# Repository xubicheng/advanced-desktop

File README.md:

# AD — 鼠标形态的无屏微型计算机

**一句话：把一台计算机做进鼠标里。没有屏幕，用语音进出，屏幕是可选外设。**

> 现状：**设计方案阶段（v4），未采购、未下单，没有可运行的样机。**
> 这不是成品仓库，是一份把「能不能做、要妥协什么」算清楚的工程档案。

---

## 这是什么

AD = Advanced Desktop，一个 DIY 研究项目：

- **硬件**：BeagleBone Black（L1 板级开源）塞进 132×76×40mm 的真鼠标外壳，重 250–300g；
- **交互**：按住说话 → 云端 STT → LLM → 云端 TTS → 喇叭播报；自身位移驱动光标；
- **屏幕**：**可选**。要么 BBB 用 micro-HDMI 直出 720p，要么由 Android 手机把 AD 自己的画面投到你的 PC 显示器上；
- **软件**：一份 Rust 核心 + 两个渲染器（Android Canvas / BBB egui）+ 一个 PC 端 Receiver（只显示帧、只注入鼠标）。

**Windows / Linux 上跑的不是「AD 的另一个版本」，只是「一台显示器 + 一只被遥控的鼠标」。**

---

## 当前阶段

| 项 | 状态 |
|---|---|
| 硬件方案 | ✅ 定稿（v3）：BBB + 720p + 成品 USB 鼠标模块 + DC 5V/4A |
| 投屏方案 | ✅ 定稿（v4）：自渲染 + 自有 Receiver（MJPEG over TCP），scrcpy 兜底 |
| Android 最小链路 | ⬜ 未开始（计划 2 周） |
| 投屏 + 反向指针 | ⬜ 未开始（计划 W3–W4） |
| BBB 硬件端 | ⬜ 未开始（等板） |
| 采购 | ⬜ **未下单**（清单已出） |

## 下一步

1. 询价 BeagleBone Black（买不到就走 BBB Wireless）；
2. 按 [Android 先行周计划](docs/v3/Android-先行-周计划.md) 跑 W1–W2 语音链路；
3. W3 投屏、W4 反向指针；
4. 硬件端最后接。

---

## 文档索引

| 文档 | 看什么 |
|---|---|
| [**v4 方案（当前）**](docs/v4/AD-鼠标形无屏微型计算机-设计方案-v4.md) | 概念模型、投屏三方案取舍、数据流图、反向输入、息屏实测 |
| [v3 方案（硬件基线）](docs/v3/AD-鼠标形无屏微型计算机-设计方案-v3.md) | 六项连带代价、720p、USB Hub、供电、散热重算、验收表 |
| [Android 先行周计划](docs/v3/Android-先行-周计划.md) | 2 周排期 + 15 条验收线 |
| [许可清单](docs/v3/许可清单.md) | 组件许可、GPL 隔离、模型权重核实状态 |
| [采购清单（淘宝优先）](docs/v3/采购清单-淘宝优先.md) | 表 A 淘宝 / 表 B 线下 / 总预算 |
| [MVP 手工样品清单](docs/MVP-checklist/MVP-手工样品实施清单.md) | 买料 → 焊 → 装 → 测，每步通过标准 |
| [**决策记录 DECISIONS**](docs/DECISIONS.md) | D1–D5 为什么这么定，以及没关闭的问题 |
| [变更记录 CHANGELOG](docs/CHANGELOG.md) | v1→v4 每次改了什么、为什么、推翻了什么 |
| [文档总索引](docs/README.md) | 全部文档的导航 |

---

## 三个必须先知道的硬事实

1. **单核 1GHz + 512MB 跑不动本地语音。** 3 秒音频在 BBB 上要 9–15 秒才出结果。所以语音默认走云端，本地只留 6–10 条预录提示音。这不是偷懒，是算力事实。
2. **720p 是上限。** TDA19988 与单核显示子系统撑不住 1080p 的日常使用，UI 按 1280×720 设计（正文 ≥24px、按钮 ≥64px、禁双栏）。
3. **鼠标会很重（250–300g）。** 常规重鼠约 120–140g。这是「L1 开源板 + 真鼠标形态」的必然代价，缓解手段是重心压在掌心，不是减重。

---

## 在手机上看进度

**客户端的账号同步不是本仓库能控制的**——你在 A 电脑上的对话不会自动出现在 B 电脑或手机上。

本项目的跨设备查看机制是：**GitHub 公开仓库 + 每次更新即提交。**

手机上：

1. 用手机浏览器打开 <https://github.com/xubicheng/advanced-desktop>；
2. 点 **Commits** 看最近改了什么（每条提交信息都写清改了什么）；
3. 看根目录 **README** 的「当前阶段」表格 —— 这张表每次更新都会改；
4. 想看细节就点 `docs/` 下的 Markdown，GitHub 手机版能直接渲染。

不需要装 App，不需要登录。

---

## 目录结构

```
advanced-desktop/
├─ docs/        v1 / v2 / v3 / v4 版本化方案 + CHANGELOG + DECISIONS + README 索引
├─ software/    核心（Rust）/ Android 壳 / BBB 壳 / PC Receiver
├─ hardware/    外壳（FreeCAD/OpenSCAD）、转接板（KiCad）、装配图
├─ bom/         采购清单 CSV（淘宝 / 线下）
└─ logs/        对话纪要（已脱敏）
```

---

## 许可

- 代码 **MIT**（[LICENSE-CODE](LICENSE-CODE)）
- 硬件设计 **CERN-OHL-S-2.0**（[LICENSE-HARDWARE](LICENSE-HARDWARE)）
- 文档 **CC-BY-4.0**（[LICENSE-DOCS](LICENSE-DOCS)）
- 说明与第三方组件：[LICENSE](LICENSE)、[THIRD-PARTY.md](THIRD-PARTY.md)

## 兼容基线

| 平台 | 支持 |
|---|---|
| Windows | 10 1809（17763）+、Windows 11 |
| Linux | glibc ≥ 2.28：Ubuntu 20.04/22.04/24.04、Rocky 8/9、Alma 8/9 |
| Linux（不支持） | **CentOS 7（glibc 2.17，已 EOL）**、CentOS 8（已 EOL） |
| Android | 8.0（API 26）+ |
| macOS / iOS | 不做 |

---

*这是一个仍在设计阶段的 DIY 项目。所有价格、供货、性能数字凡未实测的都已标注「需询价 / 需实测」。*

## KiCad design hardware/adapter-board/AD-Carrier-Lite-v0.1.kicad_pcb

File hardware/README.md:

# hardware/ — 外壳、转接板、装配图

```
hardware/
├─ enclosure/        外壳：FreeCAD 参数化模型 + OpenSCAD 备选 + 打印参数
├─ adapter-board/    载板/转接板：KiCad 工程（电源保护 + Hub 供电 + 排针 + 按键）
└─ assembly/         装配图、爆炸图、螺丝与走线表
```

## 状态

- `adapter-board/`：**Carrier-Lite v0.1 草案已出板**（60×45mm，2 层），含 Gerber、BOM、坐标、STEP、预览与制板说明，见 [FAB-NOTES.md](adapter-board/FAB-NOTES.md)。未出原理图，尺寸待实测。
- `enclosure/`、`assembly/`：**仍为空骨架。** 设计参数已定，图纸尚未出。

## 已定的关键参数（照此建模）

| 项 | 值 | 出处 |
|---|---|---|
| 外形 | **132 × 76 × 40 mm** | v3 §3.1 |
| 内部净高 | ≥ 24 mm（RJ45 13.5mm 为最高元件） | v3 §3.1 |
| 主板 | BeagleBone Black，86.36 × 53.34 × 1.6 mm | 官方 |
| 壁厚 | 2.4–3.0 mm | v3 §6.2 |
| 材质 | **ABS**（主体）+ **5052 铝 1.5mm**（底盖兼配重） | v3 §6.2 |
| 开孔率 | 总 3.3–3.6%（侧面进风 φ2×6×2，底部后段出风 φ2×12） | v3 §6.3 |
| 顶面 | **不开孔**（手感 / 进灰 / 烫手） | v3 §6.3 |
| 散热片 | 铝 20×20×8 + 导热垫 1.0mm ≥3W/mK | v3 §6.4 |
| 光学高度 | 按实测的鼠标模块定，配 0.5/1.0/1.5mm 三档垫片 | v3 §4.4 |

## 许可

**CERN-OHL-S-2.0**（强互惠）。改过的设计必须以同一许可公开。

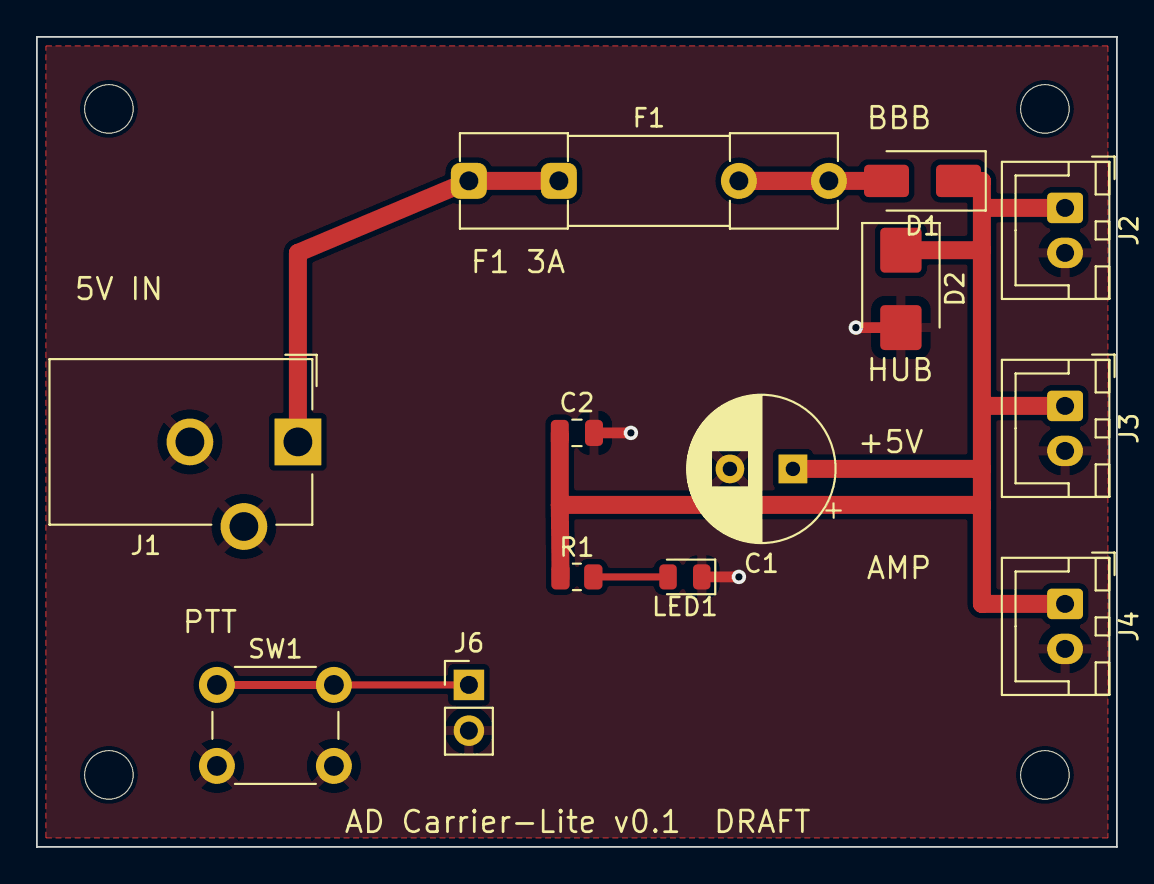
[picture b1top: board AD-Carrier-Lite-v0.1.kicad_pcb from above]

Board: 2 copper layers, 60.0 x 45.0 mm, 17 parts (0 on the bottom side), 6 nets.

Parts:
C1: 470uF 10V; CP_Radial_D8.0mm_P3.50mm
C2: 100nF 50V; C_0805_2012Metric
D1: SS54; D_SMA
D2: SMAJ5.0A; D_SMB
F1: 3A slow-blow; Fuseholder_Clip-5x20mm_Littelfuse_111_Inline_P20.00x5.00mm_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
H1, H2, H3, H4: MountingHole_2.7mm_M2.5
J1: DC 5.5x2.1; BarrelJack_CUI_PJ-102AH_Horizontal
J2: 5V OUT BBB; JST_XH_B2B-XH-A_1x02_P2.50mm_Vertical
J3: 5V OUT HUB; JST_XH_B2B-XH-A_1x02_P2.50mm_Vertical
J4: 5V OUT AMP; JST_XH_B2B-XH-A_1x02_P2.50mm_Vertical
J6: PTT GPIO; PinHeader_1x02_P2.54mm_Vertical
LED1: Green; LED_0805_2012Metric
R1: 1k; R_0805_2012Metric
SW1: PTT; SW_PUSH_6mm

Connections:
5V_IN: F1.1, J1.1
+5V: C1.1, C2.1, D1.1, D2.1, J2.1, J3.1, J4.1, R1.1
FUSED: D1.2, F1.2
GND: C1.2, C2.2, D2.2, J1.2, J1.3, J2.2, J3.2, J4.2, J6.2, LED1.1, SW1.2
LED_A: LED1.2, R1.2
PTT: J6.1, SW1.1

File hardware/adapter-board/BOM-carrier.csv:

Reference,Qty,Description,Package,MPN / Part,Notes
J1,1,DC 5.5x2.1 barrel jack,THT horizontal,CUI PJ-102AH,center positive
F1,1,Fuse holder + 3A slow-blow,5x20mm THT,Littelfuse 111 + 0213003.MXP,do not use 1.1A resettable
D1,1,SS54,SMA,SS54,"40V 5A Schottky, reverse protection"
D2,1,SMAJ5.0A,SMB,SMAJ5.0A,unidirectional TVS
C1,1,470uF 10V,Radial D8 P3.5,Generic,"low ESR, height <=12mm"
C2,1,100nF 50V X7R,0805,Generic,decoupling
R1,1,1k 1%,0805,Generic,LED current limit
LED1,1,Green LED,0805,Generic,power indicator
"J2,J3,J4",3,JST XH 2P,THT vertical,JST B2B-XH-A,"5V/GND: BBB, HUB, AMP"
SW1,1,6x6x5 tact switch,THT,Generic,"PTT, one side to GND"
J6,1,2.54mm 1x2 header,THT vertical,Generic,PTT signal to GPIO
H1-H4,4,M2.5 mounting hole,NPTH 2.7mm,-,mechanical only
